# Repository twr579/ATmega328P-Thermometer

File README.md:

# ATmega328P Thermometer
This repository contains code, PCB, and enclosure design for a thermometer based on the ATmega328P microcontroller.

I was inspired to work on this project because of my lack of a portable, lightweight thermometer to take on hiking/camping trips. I've previously relied on my phone's weather app and woken up with a frost-covered sleeping bag as a result, so having a thermometer on hand is a useful tool for testing the efficacy of my sleep system.

The code was written  and tested in Arduino IDE.

Schematic and PCB were designed in KiCad.

Enclosure was designed in Fusion 360.

## List of Materials
* [ATmega328P-PU](https://www.digikey.com/en/products/detail/microchip-technology/ATMEGA328P-PU/1914589)
* [JST 2-pin Connector Header](https://www.digikey.com/en/products/detail/jst-sales-america-inc/S2B-PH-K-S/926626)
* [Lithium Ion Polymer Battery - 3.7v 500mAh](https://www.adafruit.com/product/1578)
* [Right Angle Slide Switch](https://www.digikey.com/en/products/detail/c-k/OS102011MA1QN1/1981430)
* [L4931CZ33-AP Voltage Regulator](https://www.digikey.com/en/products/detail/stmicroelectronics/L4931CZ33-AP/1038129)
* [16MHz Crystal Oscillator](https://www.sparkfun.com/products/536)
* [Temperature Sensor - TMP36](https://www.sparkfun.com/products/10988)
* 2x Single Digit 7-segment Display
* 3x 10uF Electrolytic Capacitor
* 2x 22pF Ceramic Capacitor
* 10k Ohm Resistor

## Schematic

## PCB

## 3D Model

## Enclosure

## Final Product - Without Enclosure

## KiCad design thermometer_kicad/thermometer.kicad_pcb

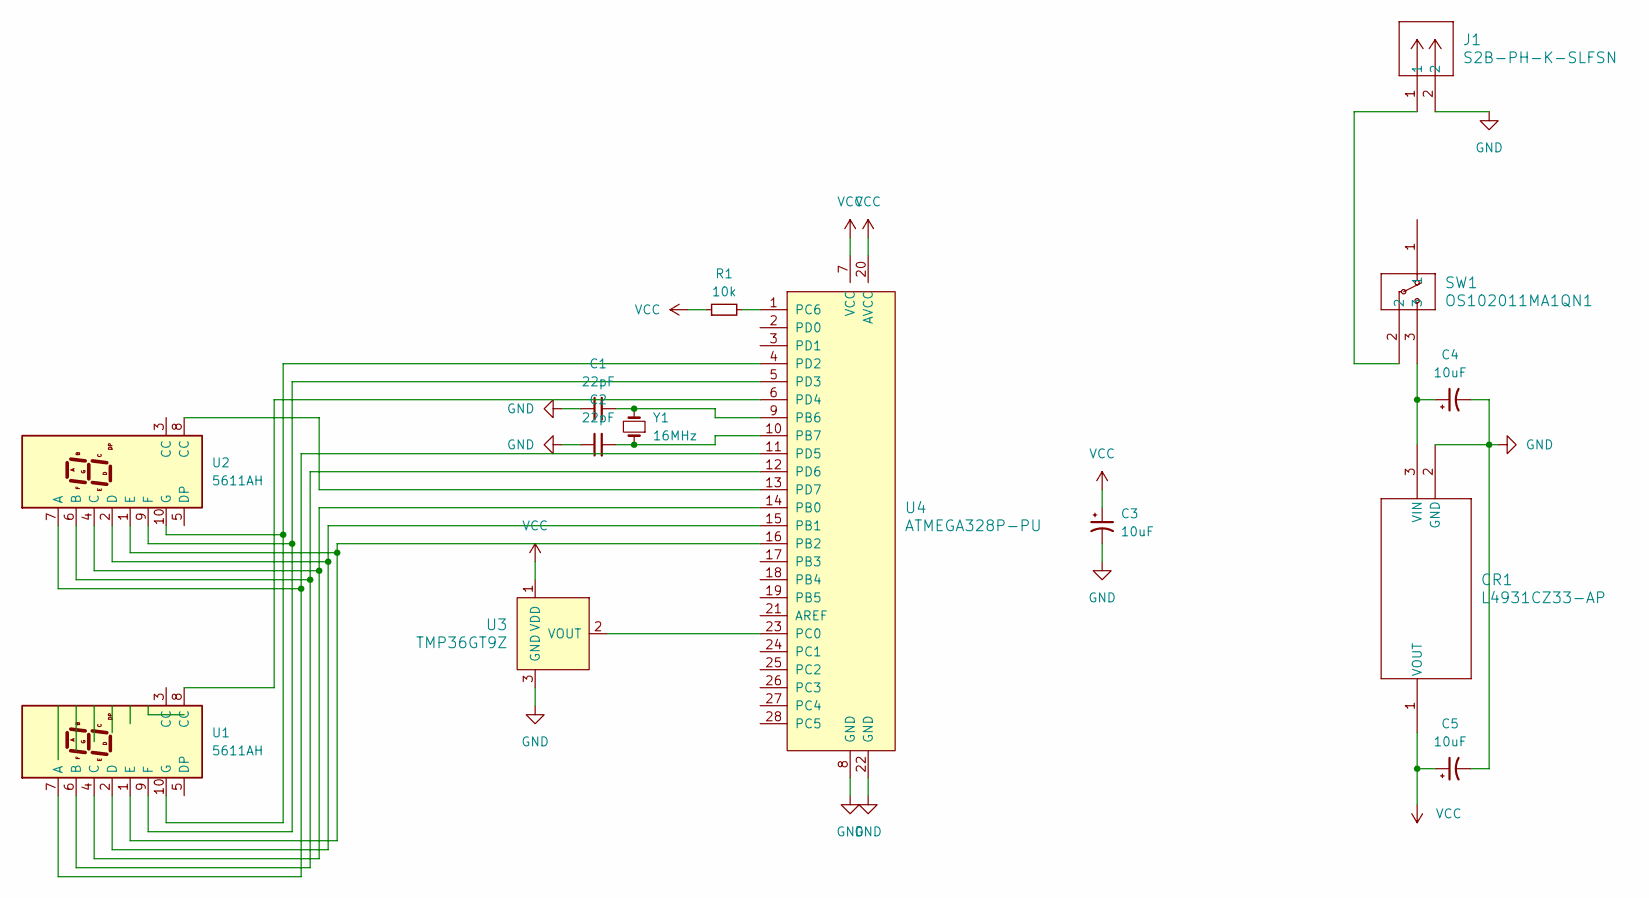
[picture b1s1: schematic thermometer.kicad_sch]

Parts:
C1, C2: 22pF; C_Disc_D3.0mm_W2.0mm_P2.50mm
C3, C4, C5: 10uF; CP_Radial_D4.0mm_P2.00mm
CR1: L4931CZ33-AP; TO-92-TR_STM
J1: S2B-PH-K-SLFSN; CONN_S2B-PH-K-S_JST
R1: 10k; R_Axial_DIN0207_L6.3mm_D2.5mm_P7.62mm_Horizontal
SW1: OS102011MA1QN1; OS102011MA1QN1_CNK
U1, U2: 5611AH
U3: TMP36GT9Z; TO-92-3; MPN TMP36GT9Z; Digi-Key_PN TMP36GT9Z-ND
U4: ATMEGA328P-PU; DIP-28_W7.62mm; MPN ATMEGA328P-PU; Digi-Key_PN ATMEGA328P-PU-ND
Y1: 16MHz; Crystal_HC49-U_Vertical

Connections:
GND: C1.1, C2.1, C3.2, C4.2, C5.2, CR1.2 (GND), J1.2, U3.3 (GND), U4.8 (GND), U4.22 (GND)
unnamed: C4.1, CR1.3 (VIN), SW1.3
unnamed: J1.1, SW1.2
unnamed: U1.7 (A), U2.7 (A), U4.11 (PD5)
unnamed: U1.6 (B), U2.6 (B), U4.12 (PD6)
unnamed: U1.4 (C), U2.4 (C), U4.14 (PB0)
unnamed: U1.2 (D), U2.2 (D), U4.15 (PB1)
unnamed: U1.1 (E), U2.1 (E), U4.16 (PB2)
unnamed: U1.9 (F), U2.9 (F), U4.5 (PD3)
unnamed: U1.10 (G), U2.10 (G), U4.4 (PD2)
unnamed: U3.2 (VOUT), U4.23 (PC0)
unnamed: C1.2, U4.9 (PB6), Y1.2
unnamed: C2.2, U4.10 (PB7), Y1.1
unnamed: R1.2, U4.1 (PC6)
unnamed: U1.8 (CC), U4.6 (PD4)
unnamed: U2.8 (CC), U4.13 (PD7)
VCC: C3.1, C5.1, CR1.1 (VOUT), R1.1, U3.1 (VDD), U4.7 (VCC), U4.20 (AVCC)

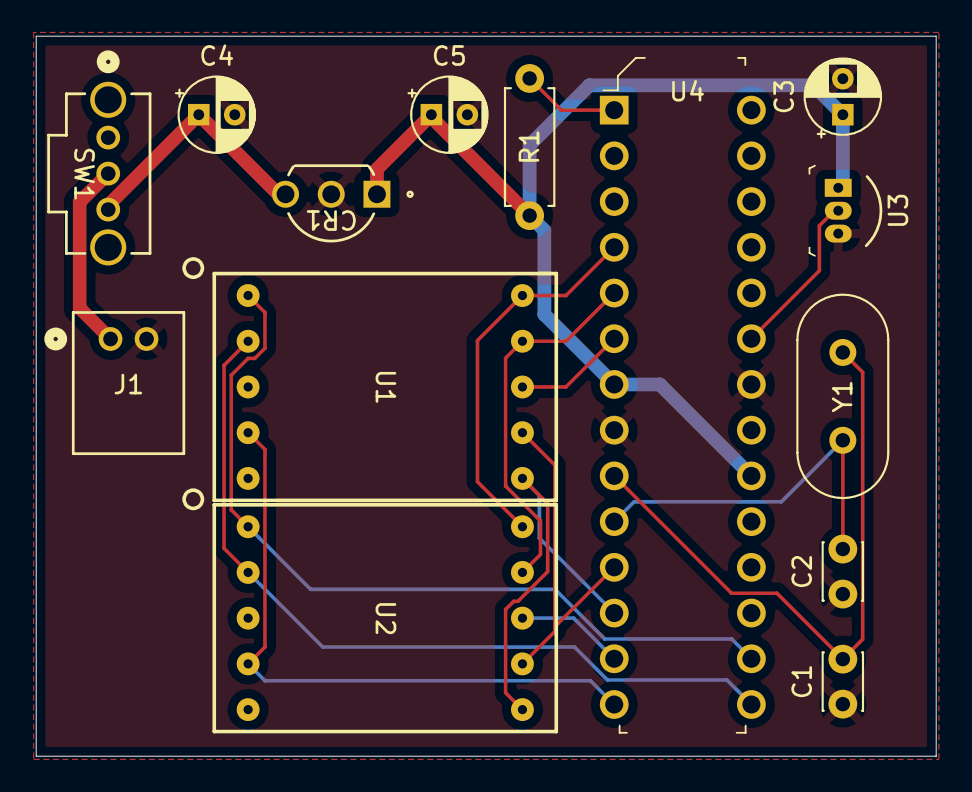
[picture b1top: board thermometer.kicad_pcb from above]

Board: 2 copper layers, 50.0 x 40.0 mm, 14 parts (0 on the bottom side), 17 nets.

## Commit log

2024-09-09 Add images
